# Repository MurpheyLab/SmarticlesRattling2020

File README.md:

# SmarticlesRattling2020

This repository includes all the hardware design and software files for the smarticle system. Examples can be found in "SmarticlePlatform/Code/Python/Examples". See [Smarticle Tracking](https://github.com/MurpheyLab/SmarticleTracking) for a python AprilTag tracking library and our MATLAB simulation in "SmarticleSimulation."  

All documentation for the python modules in this repository is available [here](https://murpheylab.github.io/SmarticlesNU/)

Installing Python Dependencies
------------

You can install pyserial and the XBee Python library using pip

    $ pip install pyserial
    $ pip install digi-xbee

Running Your First Program
-----------
Use the included `SmarticleSyncGait.py` to test your setup. You will have to modify `PORT_NAME` to match the USB port name of the local XBee connected to your computer.  

Run the the following command to execute the code and keep the python script open  
    
    $ python3 -i SmarticleSyncGait.py
    
Then you can run this command to run the smarticles for 1 minute  

    >>> timed_sync(1)

Interfacing with The Xbees
---
To Change the settings of the Base Xbee, use [DIGI XCTU](https://www.digi.com/resources/documentation/digidocs/90001526/tasks/t_download_and_install_xctu.htm)  
The Settings for the base Xbee are the default settings for 802.15.4 firmware with these changes:  
<br>
        **1.** Change mode (AP) to API Enabled  
        **2.** Change Pan ID (ID) to 1984  
        **3.** Ensure address (MY) is 0  
        **4.** Change Destination Low Address (DL) to 0xFFFF (broadcast)  
        
You can also modify these settings in a simple serial console by entering command mode. See this [guide](https://cdn.sparkfun.com/learn/materials/29/22AT%20Commands.pdf) for more information.
    
Modifying Code on The Smarticles
---
To modify the code on the smarticles themselves, you will also need to instal MiniCore into the Arduino IDE and an SI Labs driver for the CP2104 chip.  
  <br> 
    Get the CP210x Driver for your OS: [SI Labs Drivers Link](https://www.silabs.com/products/interface/usb-bridges/classic-usb-bridges/device.cp2104?q=cp2104;page=1;x6=searchHeader;q6=Software)  
    Download Arduino IDE: [Arduino IDE Link](https://www.arduino.cc/en/Main/Software)  
    Follow the instructions to install in Arduino IDE: [MiniCore Link](https://github.com/MCUdude/MiniCore#how-to-install) 
    <br>
    
After Installing all these dependencies you will have to move the files from the Code/Arduino folder into your local Arduino folder (usually found in documents)  
<br>
        **1.**  Move the programmable_smarticle folder into your Arduino directory (should be then documents/Arduino/programmable_smarticle)  
        **2.**  Move the contents of the repo Arduino/libraries folder into your local Arduino/libraries folder  
    
You will have to restart the Arduino IDE and then you should be able to open the programmable_smarticle.ino sketch and you should see PWMServo, NeoHWSerial, and Smarticle in the Sketch->Include Library file menu.

To upload the program to the smarticle, use the follow board configuration under the tools file menu:  

  | Field | Value|
|:------------:|:-------------------------------:| 
| Board        | ATmega328                      | 
| Clock        | 8MHz External                   |  
| BOD          | BOD 2.7V                        |  
| Compiler LTO | LTO Enabled                     |  
| Variant      | 328PB                           |  
| Bootloader   | Yes (UART0)                     |  
| Port         | select USB port of SI Labs Chip |

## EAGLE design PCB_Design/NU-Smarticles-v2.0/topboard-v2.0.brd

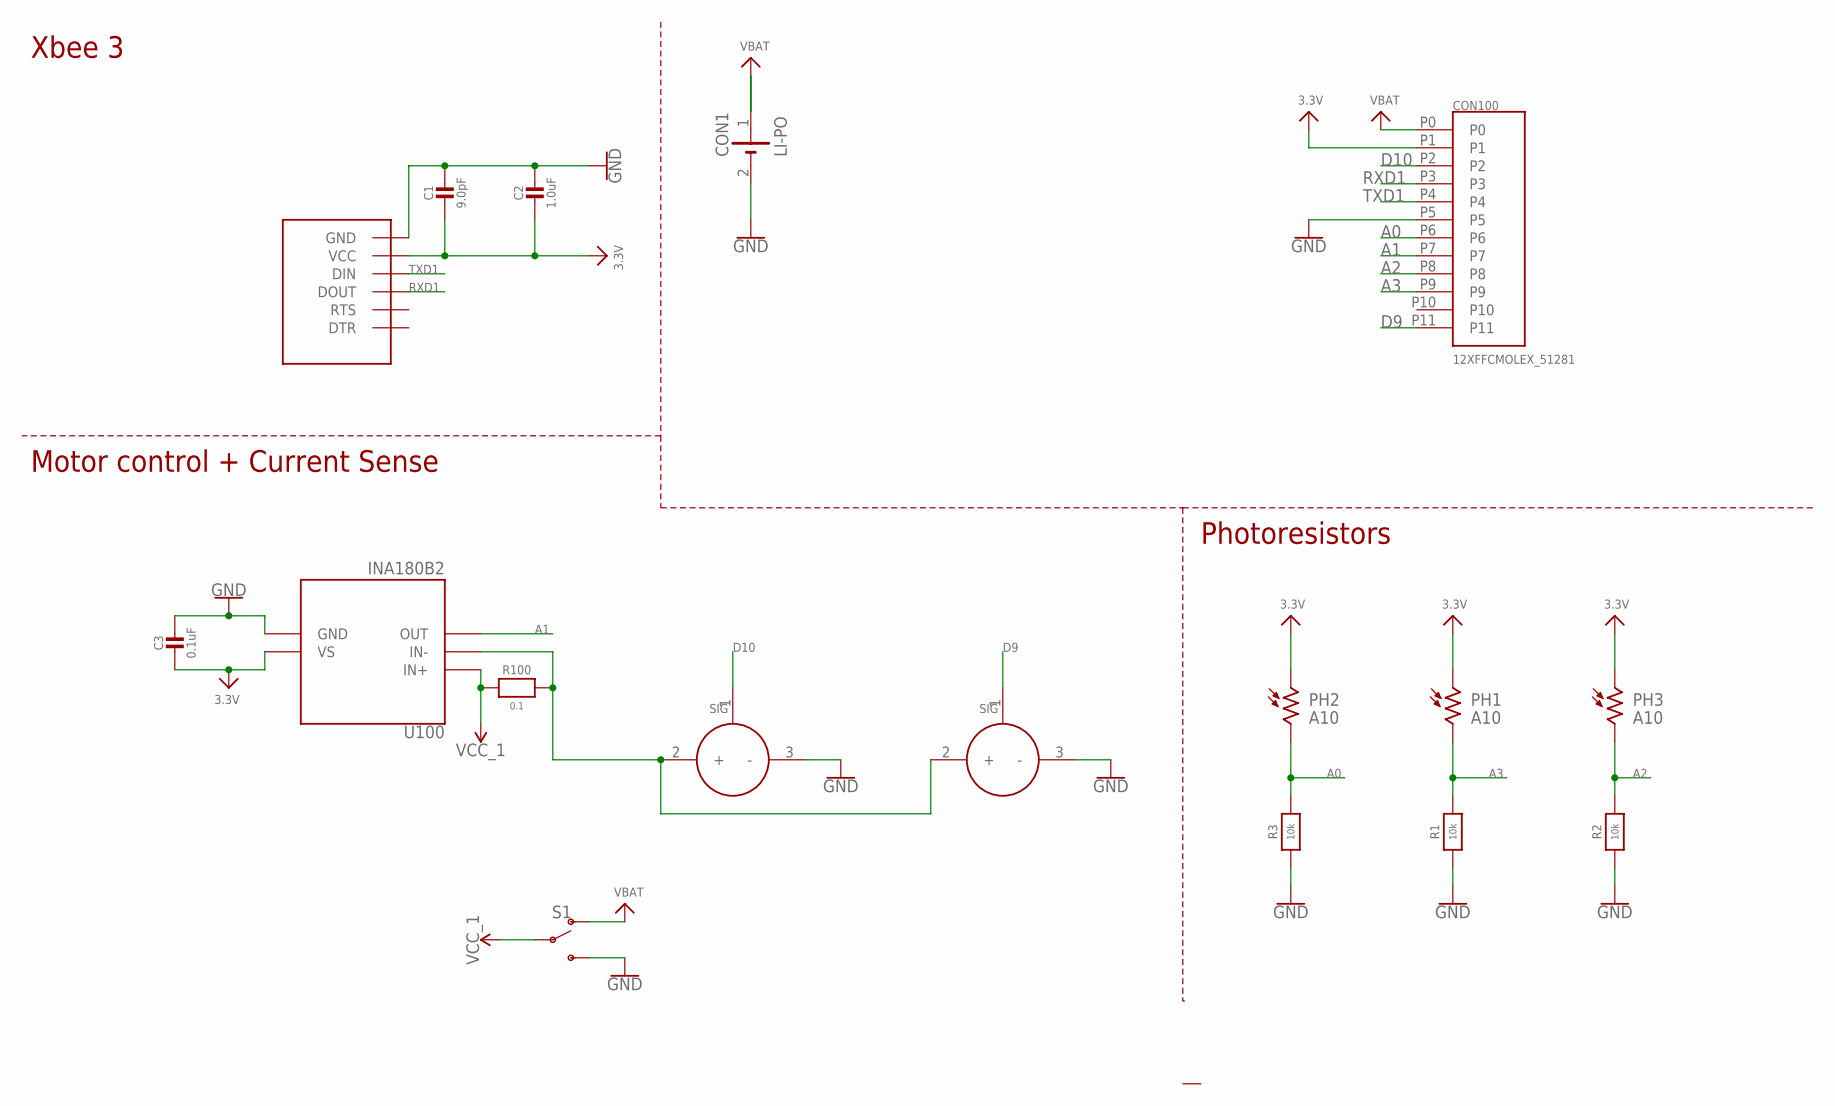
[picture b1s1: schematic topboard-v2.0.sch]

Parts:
C1: 9.0pF; _0603MP
C2: 1.0uF; _0603MP
C3: 0.1uF; _0603MP
CON1: LI-PO; 1X02_BATT
CON100: 12XFFCMOLEX_51281; MOLEX_51281-1294
M1, M2: SERVO; 1X03_SERVO
PH1, PH2, PH3: A10; PHOTORESISTOR
R1, R2, R3: 10k; _0603MP
R100: 0.1; _0603MP
S1: SWITCH-SPDT-SMD-RIGHT-ANGLE; SWITCH_SPST_SMD_A
U1: XBEE3; XBEE3_MICRO
U100: INA180B2; SOT23-5

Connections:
3.3V: C1.2, C2.2, C3.2, CON100.P1, PH1.1, PH2.1, PH3.1, U1.VCC, U100.5 (VS)
A0: CON100.P6, PH2.2, R3.2
A1: CON100.P7, U100.4 (OUT)
A2: CON100.P8, PH3.2, R2.2
A3: CON100.P9, PH1.2, R1.2
D9: CON100.P11, M1.1 (SIG)
D10: CON100.P2, M2.1 (SIG)
GND: C1.1, C2.1, C3.1, CON1.2 (-), CON100.P5, M1.3 (-), M2.3 (-), R1.1, R2.1, R3.1, S1.3 (S), U1.GND1 (GND), U1.GND2 (GND), U1.GND3 (GND), U1.GND4 (GND), U1.GND5 (GND), U1.GND6 (GND), U100.2 (GND)
unnamed: M1.2 (+), M2.2 (+), R100.2, U100.3 (IN-)
RXD1: CON100.P3, U1.DOUT/DIO13 (DOUT)
TXD1: CON100.P4, U1.DIN/CONFIG/DIO14 (DIN)
VBAT: CON1.1 (+), CON100.P0, S1.1 (O)
VCC_1: R100.1, S1.2, U100.1 (IN+)

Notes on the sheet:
Xbee 3
Photoresistors
Motor control + Current Sense

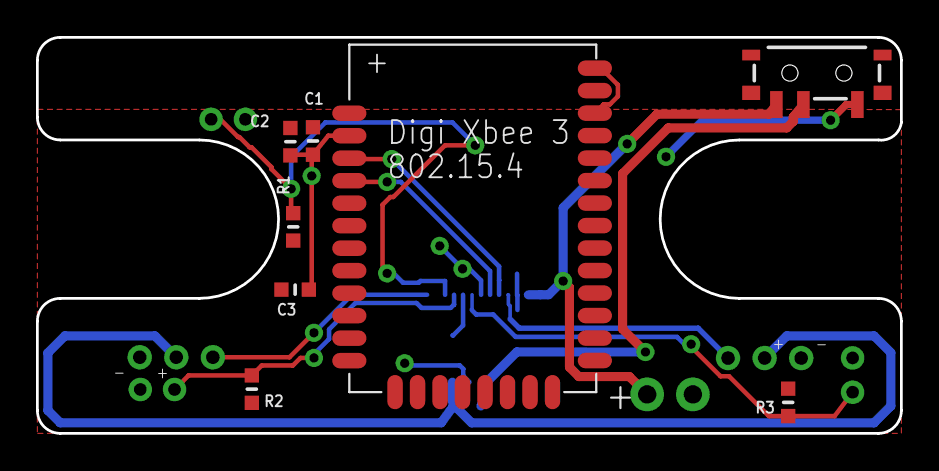
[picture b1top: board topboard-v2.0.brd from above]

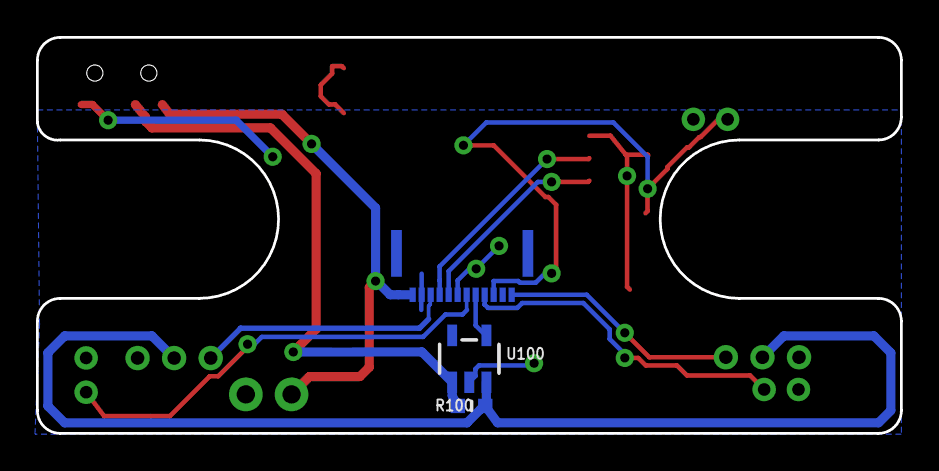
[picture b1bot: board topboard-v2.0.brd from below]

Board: 2 copper layers, 48.0 x 22.0 mm, 17 parts (3 on the bottom side), 13 nets.

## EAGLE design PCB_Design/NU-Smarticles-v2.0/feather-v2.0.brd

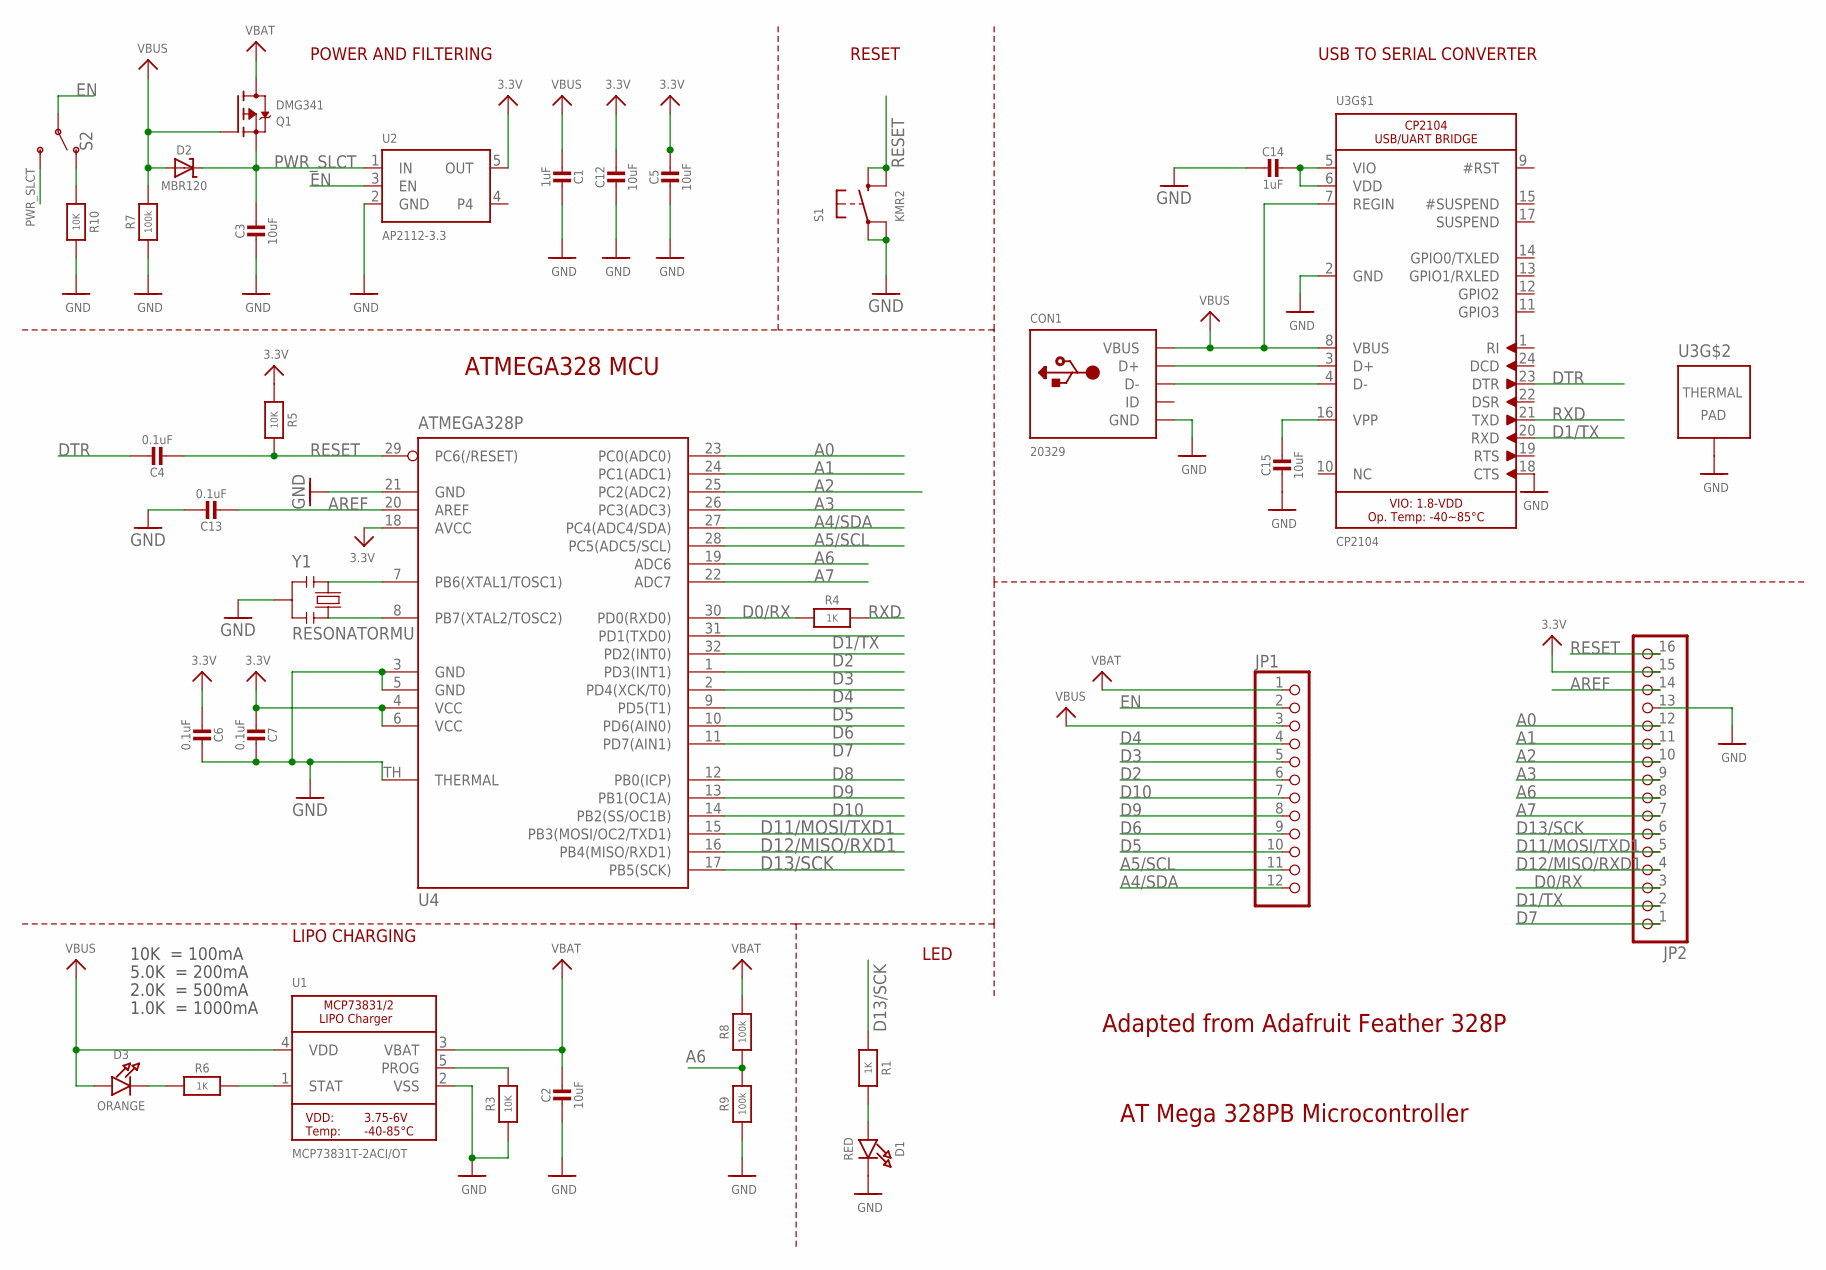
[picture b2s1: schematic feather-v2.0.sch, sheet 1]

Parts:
C1, C14: 1uF; _0603MP
C2, C3, C5, C12, C15: 10uF; _0603MP
C4, C6, C7, C13: 0.1uF; _0603MP
CON1: 20329; 4UCONN_20329_V2
D1: RED; CHIPLED_0603_NOOUTLINE
D2: MBR120; SOD-323
D3: ORANGE; CHIPLED_0603_NOOUTLINE
JP1: HEADER-1X12; 1X12_ROUND
JP2: HEADER-1X16ROUND; 1X16_ROUND
Q1: DMG341; SOT23-R
R1, R4, R6: 1K; _0603MP
R3, R5, R10: 10K; _0603MP
R7, R8, R9: 100k; _0603MP
S1: KMR2; BTN_KMR2_4.6X2.8
S2: SWITCH-SPDT-SMD-RIGHT-ANGLE; SWITCH_SPST_SMD_A
U1: MCP73831T-2ACI/OT; SOT23-5
U2: AP2112-3.3; SOT23-5
U3: CP2104; QFN24_4MM_SMSC
U4: ATMEGA328P; MLF32-TH
Y1: RESONATORMU; RESONATOR

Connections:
3.3V: C5.1, C6.2, C7.2, C12.1, JP2.15, R5.2, U2.5 (OUT), U4.4 (VCC), U4.6 (VCC), U4.18 (AVCC); also elsewhere on the board
A0: JP2.12, U4.23 (PC0(ADC0)); also elsewhere on the board
A1: JP2.11, U4.24 (PC1(ADC1)); also elsewhere on the board
A2: JP2.10, U4.25 (PC2(ADC2)); also elsewhere on the board
A3: JP2.9, U4.26 (PC3(ADC3)); also elsewhere on the board
A4/SDA: JP1.12, U4.27 (PC4(ADC4/SDA)); also elsewhere on the board
A5/SCL: JP1.11, U4.28 (PC5(ADC5/SCL)); also elsewhere on the board
A6: JP2.8, R8.1, R9.2, U4.19 (ADC6)
A7: JP2.7, U4.22 (ADC7); also elsewhere on the board
AREF: C13.2, JP2.14, U4.20 (AREF)
D0/RX: JP2.3, R4.1, U4.30 (PD0(RXD0))
D1/TX: JP2.2, U3.20 (RXD), U4.31 (PD1(TXD0))
D2: JP1.6, U4.32 (PD2(INT0))
D3: JP1.5, U4.1 (PD3(INT1))
D4: JP1.4, U4.2 (PD4(XCK/T0))
D5: JP1.10, U4.9 (PD5(T1))
D6: JP1.9, U4.10 (PD6(AIN0))
D7: JP2.1, U4.11 (PD7(AIN1)); also elsewhere on the board
D8: U4.12 (PB0(ICP))
D9: JP1.8, U4.13 (PB1(OC1A)); also elsewhere on the board
D10: JP1.7, U4.14 (PB2(SS/OC1B)); also elsewhere on the board
D11/MOSI/TXD1: JP2.5, U4.15 (PB3(MOSI/OC2/TXD1)); also elsewhere on the board
D12/MISO/RXD1: JP2.4, U4.16 (PB4(MISO/RXD1)); also elsewhere on the board
D13/SCK: JP2.6, R1.1, U4.17 (PB5(SCK))
DTR: C4.1, U3.23 (DTR)
EN: JP1.2, S2.2, U2.3 (EN)
GND: C1.1, C2.2, C3.2, C5.2, C6.1, C7.1, C12.2, C13.1, C14.2, C15.2, CON1.BASE@1 (GND), CON1.BASE@2 (GND), CON1.GND, CON1.SPRT@1 (GND), CON1.SPRT@2 (GND), CON1.SPRT@3 (GND), CON1.SPRT@4 (GND), D1.C, JP2.13, R3.1, R7.1, R9.1, R10.1, S1.A, S1.A' (P1), U1.2 (VSS), U2.2 (GND), U3.2 (GND), U3.18 (CTS), U3.THERM (TP), U4.3 (GND), U4.5 (GND), U4.21 (GND), U4.TH (THERMAL), Y1.2; also elsewhere on the board
unnamed: D3.C, R6.1
unnamed: CON1.D+, U3.3 (D+)
unnamed: R6.2, U1.1 (STAT)
unnamed: R3.2, U1.5 (PROG)
unnamed: D1.A, R1.2
unnamed: CON1.D-, U3.4 (D-)
unnamed: R10.2, S2.1 (O)
unnamed: U4.8 (PB7(XTAL2/TOSC2)), Y1.3
unnamed: C14.1, U3.5 (VIO), U3.6 (VDD)
unnamed: U4.7 (PB6(XTAL1/TOSC1)), Y1.1
unnamed: C15.1, U3.16 (VPP)
PWR_SLCT: C3.1, D2.C, Q1.2 (S), S2.3 (S), U2.1 (IN)
RESET: C4.2, JP2.16, R5.1, S1.B (S), S1.B' (S1), U4.29 (PC6(/RESET))
RXD: R4.2, U3.21 (TXD)
VBAT: C2.1, JP1.1, Q1.3 (D), R8.2, U1.3 (VBAT); also elsewhere on the board
VBUS: C1.2, CON1.VBUS, D2.A, D3.A, JP1.3, Q1.1 (G), R7.2, U1.4 (VDD), U3.7 (REGIN), U3.8 (VBUS)

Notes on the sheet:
POWER AND FILTERING
RESET
10K = 100mA
5.0K = 200mA
2.0K = 500mA
1.0K = 1000mA
USB TO SERIAL CONVERTER
LIPO CHARGING
LED
ATMEGA328 MCU
Adapted from Adafruit Feather 328P
AT Mega 328PB Microcontroller

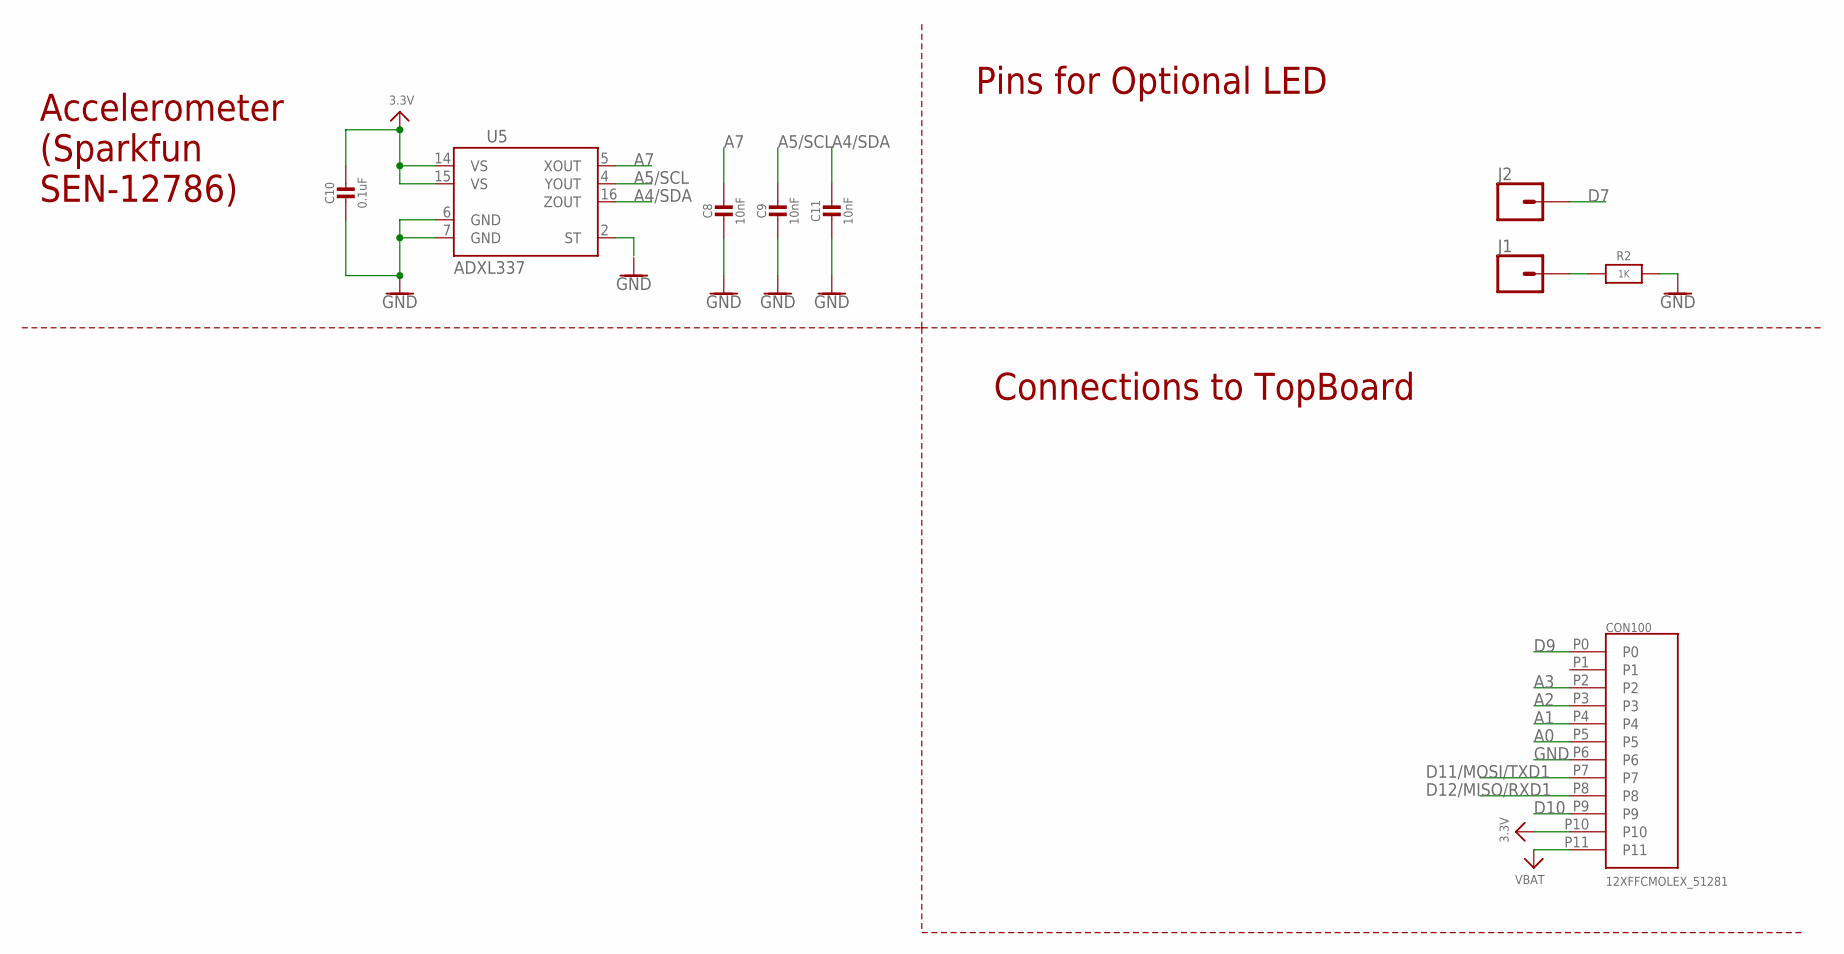
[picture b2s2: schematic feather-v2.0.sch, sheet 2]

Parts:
C8, C9, C11: 10nF; _0603MP
C10: 0.1uF; _0603MP
CON100: 12XFFCMOLEX_51281; MOLEX_51281-1294
J1, J2: CONN_01PTH_NO_SILK_YES_STOP; 1X01_NO_SILK
R2: 1K; _0603MP
U5: ADXL337; LFCSP_LQ-16

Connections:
3.3V: C10.1, CON100.P10, U5.14 (VS), U5.15 (VS); also elsewhere on the board
A0: CON100.P5; also elsewhere on the board
A1: CON100.P4; also elsewhere on the board
A2: CON100.P3; also elsewhere on the board
A3: CON100.P2; also elsewhere on the board
A4/SDA: C11.1, U5.16 (ZOUT); also elsewhere on the board
A5/SCL: C9.1, U5.4 (YOUT); also elsewhere on the board
A7: C8.1, U5.5 (XOUT); also elsewhere on the board
D7: J2.1; also elsewhere on the board
D9: CON100.P0; also elsewhere on the board
D10: CON100.P9; also elsewhere on the board
D11/MOSI/TXD1: CON100.P7; also elsewhere on the board
D12/MISO/RXD1: CON100.P8; also elsewhere on the board
GND: C8.2, C9.2, C10.2, C11.2, CON100.P6, R2.2, U5.6 (GND), U5.7 (GND); also elsewhere on the board
unnamed: J1.1, R2.1
VBAT: CON100.P11; also elsewhere on the board

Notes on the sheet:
Pins for Optional LED
Connections to TopBoard
Accelerometer (Sparkfun SEN-12786)

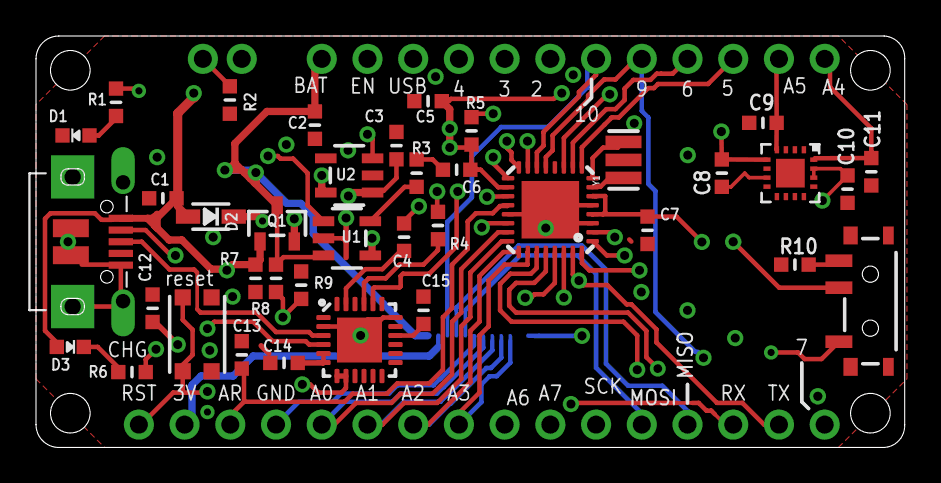
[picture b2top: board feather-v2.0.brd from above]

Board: 4 copper layers, 48.3 x 22.9 mm, 43 parts (1 on the bottom side), 43 nets.

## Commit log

2020-03-26 ignore DS Store files
2020-03-26 solidworks files
2020-03-26 PCB files
2020-03-26 microcontroller code
2020-03-26 controller code
2020-08-27 wipe clean
2020-08-27 add hardware and readme
2020-08-27 xbee profiles
2020-08-30 experimental data
2020-08-31 firmware folder
2020-09-22 add script to visualize data from experiments
2020-09-23 try to make embedded plots show on github
2020-09-25 add simulation folder
2020-09-25 add changes to smarticle firmware that alex made
2020-09-28 add license file
2020-09-28 update with DOI

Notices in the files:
parts and their libraries:
SparkFun-PowerSymbols: Licensing: Creative Commons ShareAlike 4.0 International - https://creativecommons.org/licenses/by-sa/4.0
